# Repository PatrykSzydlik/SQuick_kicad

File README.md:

**Contributors:**

Piotr Gorzelnik

Patryk Szydlik

**Project:**

Squick Micromouse

**Brief:**

Repository contains all KiCAD projects related to development of electrical schematics and PCB board project.

**Repository Content:** 

 -- 	Squick (main KiCAD project)

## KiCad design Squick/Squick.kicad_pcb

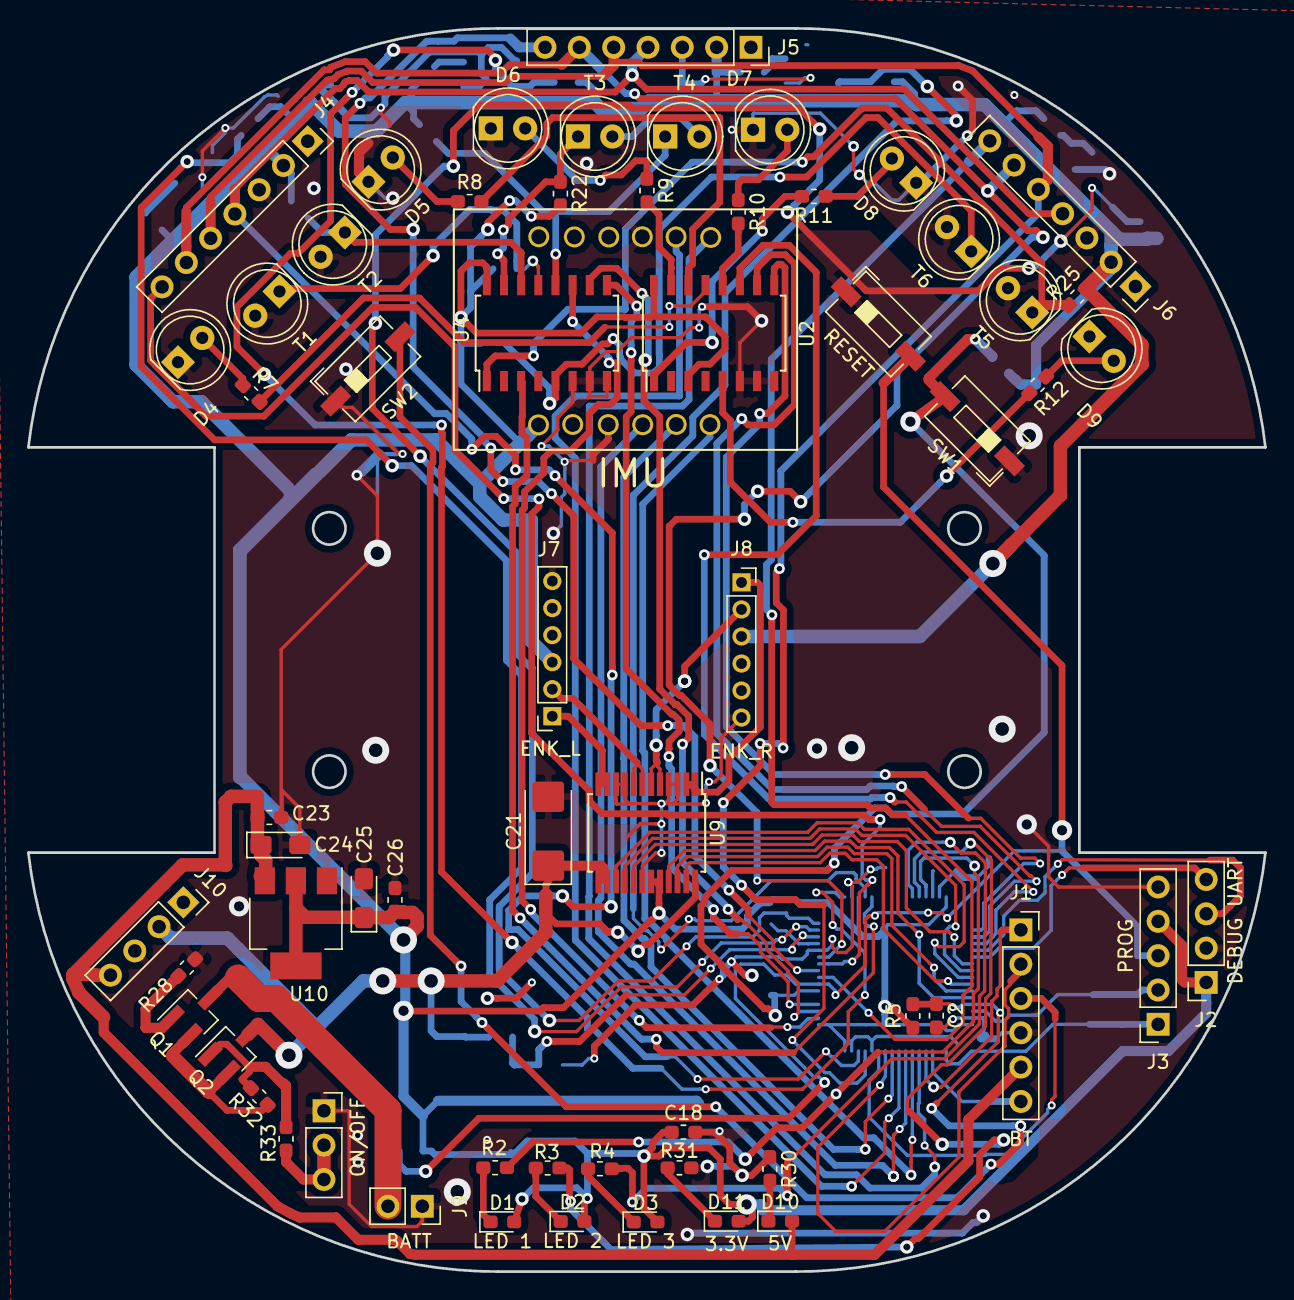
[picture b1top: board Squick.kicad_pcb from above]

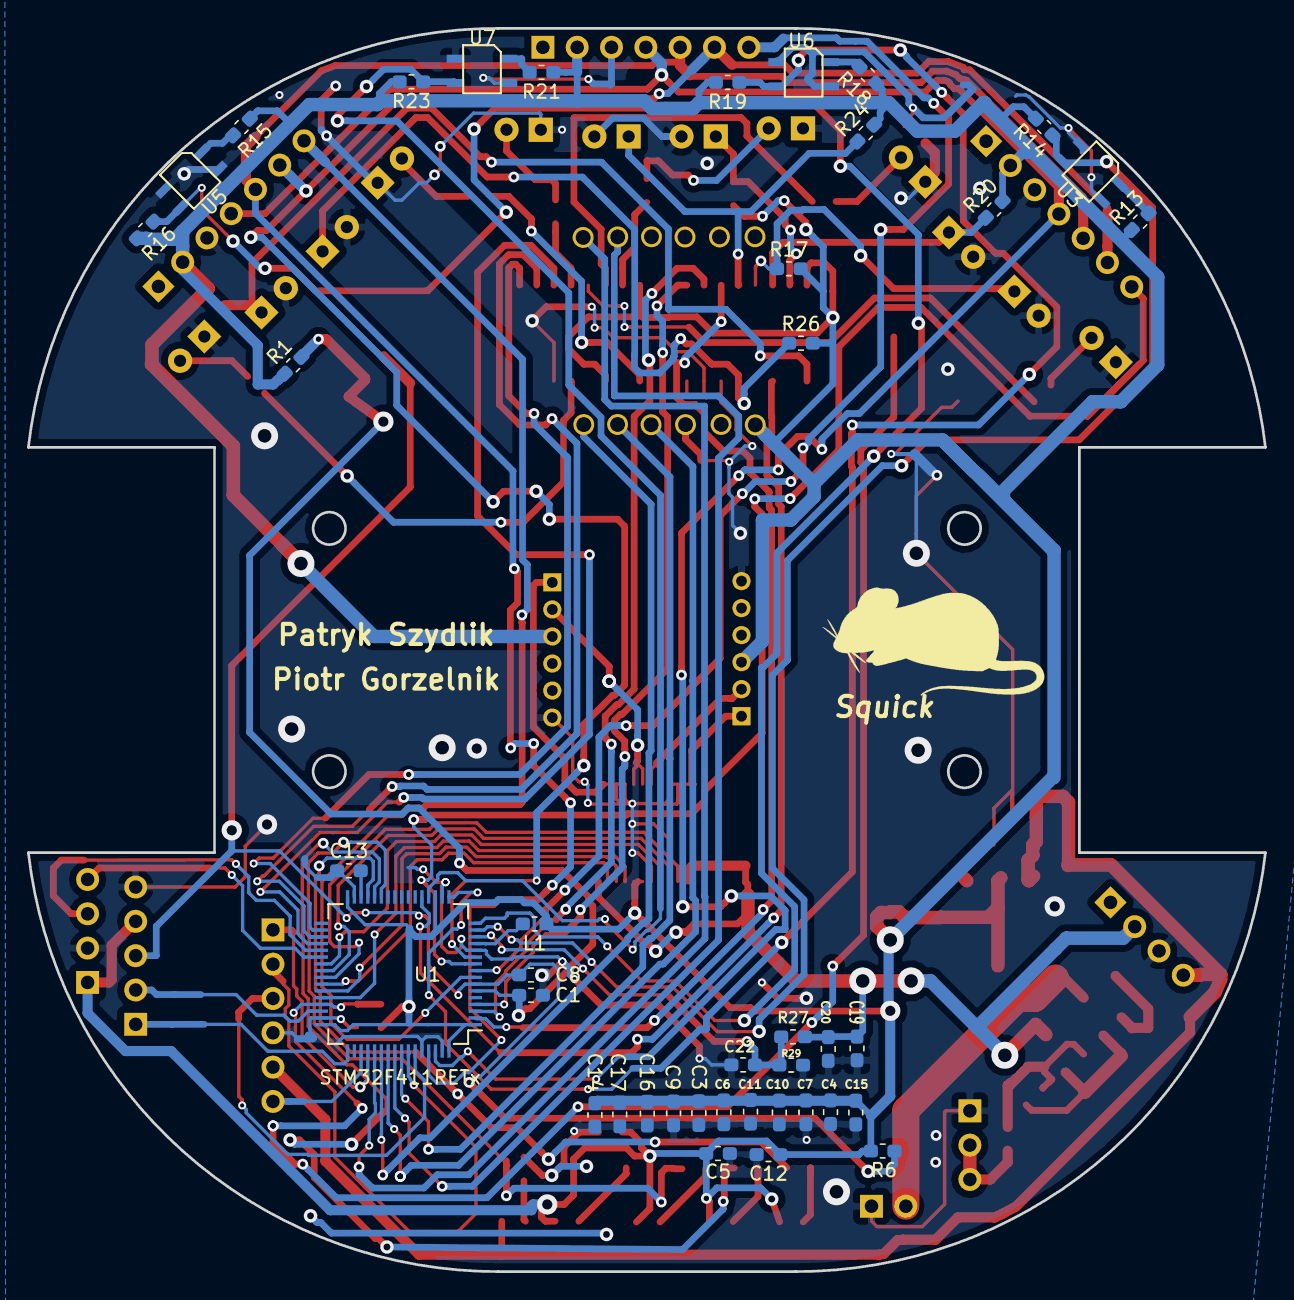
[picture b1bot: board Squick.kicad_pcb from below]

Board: 2 copper layers, 91.5 x 92.0 mm, 103 parts (41 on the bottom side), 85 nets.

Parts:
C1, C2, C3, C4, C5, C6, C7, C8, C9, C11, C14, C15, C16, C18, C19, C20, C22, C23, C26: 100n; C_0603_1608Metric_Pad1.05x0.95mm_HandSolder
C10: 1u; C_0603_1608Metric_Pad1.05x0.95mm_HandSolder
C12, C13: 4.7u; C_0603_1608Metric_Pad1.05x0.95mm_HandSolder
C17: 10u; C_0603_1608Metric_Pad1.05x0.95mm_HandSolder
C21: 22u; CP_EIA-6032-28_Kemet-C_Pad2.25x2.35mm_HandSolder
C24, C25: 10u; CP_EIA-3216-18_Kemet-A_Pad1.58x1.35mm_HandSolder
D1: LED 1; LED_0603_1608Metric_Pad1.05x0.95mm_HandSolder
D2: LED 2; LED_0603_1608Metric_Pad1.05x0.95mm_HandSolder
D3: LED 3; LED_0603_1608Metric_Pad1.05x0.95mm_HandSolder
D4: IR_1; LED_D5.0mm
D5: IR_2; LED_D5.0mm
D6: IR_3; LED_D5.0mm
D7: IR_4; LED_D5.0mm
D8: IR_5; LED_D5.0mm
D9: IR_6; LED_D5.0mm
D10: 5V; LED_0603_1608Metric_Pad1.05x0.95mm_HandSolder
D11: 3.3V; LED_0603_1608Metric_Pad1.05x0.95mm_HandSolder
J1: BT; PinSocket_1x06_P2.54mm_Vertical
J2: DEBUG UART; PinSocket_1x04_P2.54mm_Vertical
J3: PROG; PinSocket_1x05_P2.54mm_Vertical
J4: VL53L0X_L; PinSocket_1x07_P2.54mm_Vertical
J5: VL53L0X_F; PinSocket_1x07_P2.54mm_Vertical
J6: VL53L0X_R; PinSocket_1x07_P2.54mm_Vertical
J7: ENK_L; PinSocket_1x06_P2.00mm_Vertical
J8: ENK_R; PinSocket_1x06_P2.00mm_Vertical
J9: BATT; PinSocket_1x02_P2.54mm_Vertical
J10: D24V3F-5V; PinSocket_1x04_P2.54mm_Vertical
L1: 10u; L_0603_1608Metric_Pad1.05x0.95mm_HandSolder
Q1, Q2: AO3407A; SOT-23_Handsoldering
R1, R5, R6, R27: 100k; R_0603_1608Metric_Pad1.05x0.95mm_HandSolder
R2, R3, R4, R13, R15, R17, R18, R20, R21, R22, R24, R25, R26: 220; R_0603_1608Metric_Pad1.05x0.95mm_HandSolder
R7, R8, R9, R10, R11, R12: 22; R_0603_1608Metric_Pad1.05x0.95mm_HandSolder
R14, R16, R19, R23, R32: 10k; R_0603_1608Metric_Pad1.05x0.95mm_HandSolder
R28, R33: 1k; R_0603_1608Metric_Pad1.05x0.95mm_HandSolder
R29: 47k; R_0603_1608Metric_Pad1.05x0.95mm_HandSolder
R30: 470; R_0603_1608Metric_Pad1.05x0.95mm_HandSolder
R31: 330; R_0603_1608Metric_Pad1.05x0.95mm_HandSolder
SW1: USER_BUT_1; SW_DIP_SPSTx01_Slide_6.7x4.1mm_W6.73mm_P2.54mm_LowProfile_J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
SW2: USER_BUT_2; SW_DIP_SPSTx01_Slide_6.7x4.1mm_W6.73mm_P2.54mm_LowProfile_J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
SW3: RESET; SW_DIP_SPSTx01_Slide_6.7x4.1mm_W6.73mm_P2.54mm_LowProfile_J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
SW4: ON/OFF; PinSocket_1x03_P2.54mm_Vertical
T1, T2, T3, T4, T5, T6: SFH-313FA; LED_D5.0mm
U1: STM32F411RETx; LQFP-64_10x10mm_P0.5mm
U2, U4: CD4051B; SOIC-16W_5.3x10.2mm_P1.27mm
U3, U5, U6, U7: KTIR0711S
U8: Adafruit_4554; IMU_LSM9DS1_Adafruit4634
U9: TB6612FNG; SSOP-24_5.3x8.2mm_P0.65mm
U10: LM1117-3.3; SOT-223-3_TabPin2

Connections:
+3.3V: C3.1, C4.1, C5.1, C6.1, C7.2, C9.1, C10.2, C11.1, C12.2, C14.1, C15.1, C16.1, C17.1, C18.1, C25.1, C26.1, D1.2, D2.2, D3.2, D11.2, J2.1, J3.4, J4.2, J5.2, J6.2, J7.3, J8.3, L1.1, R1.1, R5.1, R6.1, R13.1, R14.2, R15.1, R16.2, R17.2, R18.1, R19.2, R20.2, R21.1, R22.2, R23.2, R24.2, R25.2, R26.2, U1.1, U1.19, U1.32, U1.48, U1.64, U2.3, U2.16, U4.16, U8.12, U9.19, U9.20, U10.2
+5V: C23.1, C24.1, D10.2, J1.5, J10.4, U10.3
BT_EN: J1.6, U1.51
BT_RX: J1.2, U1.58
BT_State: J1.1, U1.52
BT_TX: J1.3, U1.59
BUT_1: C1.1, R1.2, SW1.2, U1.6
BUT_2: C2.1, R5.2, SW2.2, U1.45
DEBUG_RX: J2.3, U1.37
DEBUG_TX: J2.4, U1.38
GND: C1.2, C2.2, C3.2, C4.2, C5.2, C6.2, C7.1, C8.2, C9.2, C10.1, C11.2, C12.1, C13.2, C14.2, C15.2, C16.2, C17.2, C18.2, C19.2, C20.2, C21.2, C22.1, C23.2, C24.2, C25.2, C26.2, D4.1, D5.1, D6.1, D7.1, D8.1, D9.1, J1.4, J2.2, J3.5, J4.3, J5.3, J6.3, J7.6, J8.6, J9.1, J10.3, R28.2, R29.1, R30.1, R31.1, SW1.1, SW2.1, SW3.1, SW4.1, T1.2, T2.2, T3.2, T4.2, T5.2, T6.2, U1.12, U1.18, U1.31, U1.47, U1.60, U1.63, U2.6, U2.7, U2.8, U3.2, U3.3, U4.6, U4.7, U4.8, U5.2, U5.3, U6.2, U6.3, U7.2, U7.3, U8.4, U8.10, U9.3, U9.4, U9.9, U9.10, U9.18, U10.1
IMU_CS: U1.53, U8.6
IMU_INT: U1.54, U8.7
IR_1: R7.2, U2.13
IR_2: R8.2, U2.14
IR_3: R9.2, U2.15
IR_4: R10.2, U2.12
IR_5: R11.2, U2.1
IR_6: R12.2, U2.5
IR_A: U1.36, U2.11
IR_B: U1.35, U2.10
IR_C: U1.34, U2.9
KTIR_1: R14.1, U1.15, U3.4
KTIR_2: R16.1, U1.16, U5.4
KTIR_3: R19.1, U1.17, U6.4
KTIR_4: R23.1, U1.20, U7.4
LED_1: R2.1, U1.29
LED_2: R3.1, U1.28
LED_3: R4.1, U1.27
L_IN1: U1.39, U9.17
L_IN2: U1.40, U9.16
M1_L: J7.1, U9.11, U9.12
M1_R: J8.1, U9.1, U9.2
M2_L: J7.2, U9.7, U9.8
M2_R: J8.2, U9.5, U9.6
MISO: U1.56, U8.5
MOSI: U1.57, U8.8
unnamed: C13.1, U1.30
unnamed: D1.1, R2.2
unnamed: D2.1, R3.2
unnamed: D3.1, R4.2
unnamed: D4.2, R7.1
unnamed: D5.2, R8.1
unnamed: D6.2, R9.1
unnamed: D7.2, R10.1
unnamed: D8.2, R11.1
unnamed: D9.2, R12.1
unnamed: D10.1, R30.2
unnamed: D11.1, R31.2
unnamed: Q1.1, R28.1
unnamed: Q1.2, Q2.2, R32.1
unnamed: Q2.1, R32.2, R33.1
unnamed: R13.2, U3.1
unnamed: R15.2, U5.1
unnamed: R18.2, U6.1
unnamed: R21.2, U7.1
unnamed: R33.2, SW4.2, SW4.3
PT_1: R17.1, T1.1, U4.13
PT_2: R20.1, T2.1, U4.14
PT_3: R22.1, T3.1, U4.15
PT_4: R24.1, T4.1, U4.12
PT_5: R25.1, T5.1, U4.1
PT_6: R26.1, T6.1, U4.5
PT_A: U1.2, U4.11
PT_B: U1.3, U4.10
PT_C: U1.4, U4.9
PT_MEAS: U1.21, U4.3
PWM_L: U1.41, U9.15
PWM_R: U1.42, U9.23
RESET: C8.1, J3.3, R6.2, SW3.2, U1.7
R_IN1: U1.44, U9.21
R_IN2: U1.43, U9.22
SCK: U1.55, U8.9
SCL: J4.5, J5.5, J6.5, U1.61
SDA: J4.4, J5.4, J6.4, U1.62
SYS_SWCLCK: J3.1, U1.49
SYS_SWDIO: J3.2, U1.46
VCC: J9.2, Q1.3
VDDA: L1.2, U1.13
VL_INT_F: J5.7, U1.9
VL_INT_L: J4.7, U1.10
VL_INT_R: J6.7, U1.8
VL_XSHUT: J4.6, J5.6, J6.6, U1.11
V_batt: C22.2, R27.1, R29.2, U1.14
Vin: C19.1, C20.1, C21.1, J10.2, Q2.3, R27.2, U9.13, U9.14, U9.24

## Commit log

2021-03-07 First day of work
2021-03-09 New progress in work
2021-03-09 End for today. Almost finished
2021-03-12 Updating schemes and libraries
2021-03-12 Finished electrical scheme
2021-03-13 Assigned PCB footprints to schematic symbols and added footprints for KTIR and tact switches
2021-03-14 Created footprint for IMU
2021-03-14 README.md edited online with Bitbucket
2021-03-14 Updated pin PT_MEAS
2021-03-15 Fixed footprints and symbol
2021-03-16 Progress with PCB and some footprint debugs
2021-03-17 Progress with PCB and size reducement
2021-03-20 Major progress with PCB design
2021-03-20 PCB project almost finished (without connections)
2021-03-21 Changed IMU and assigned 0603 footprints
2021-03-21 some debugs and small changes
2021-03-21 Started connecting pads
2021-03-22 Connecting is not funny anymore
2021-03-24 Optimalization of connections and some reorganizations. Light in the tunnel
2021-03-24 Almost finished. It's getting really tight
2021-03-28 Everything connected
2021-03-29 Improved via drills and added graphic symbols
2021-03-29 Made more space for BT module and 5V converter
2021-03-30 PCB project done
2021-03-31 Created GND planes
2021-03-31 3 GND connections to go
2021-03-31 PCB project done!
2021-04-07 Last small debugs
2021-04-10 Wygenerowano gerbery do produkcji płytki
2021-04-12 Generated missing drill file
2021-04-25 Zaległa aktualizacja gerberów
2021-06-06 Updated schemes with hot-fixes
